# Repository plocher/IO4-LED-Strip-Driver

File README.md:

# I2C-LEDStripDriver
## License: CERN Open Hardware Licence v1.2

PWM Driver board for high current LED strips

An IO4 appliance that takes 4x PWM signals and drives 4x LED strips (RGB + White) at up to 2A each at 12v

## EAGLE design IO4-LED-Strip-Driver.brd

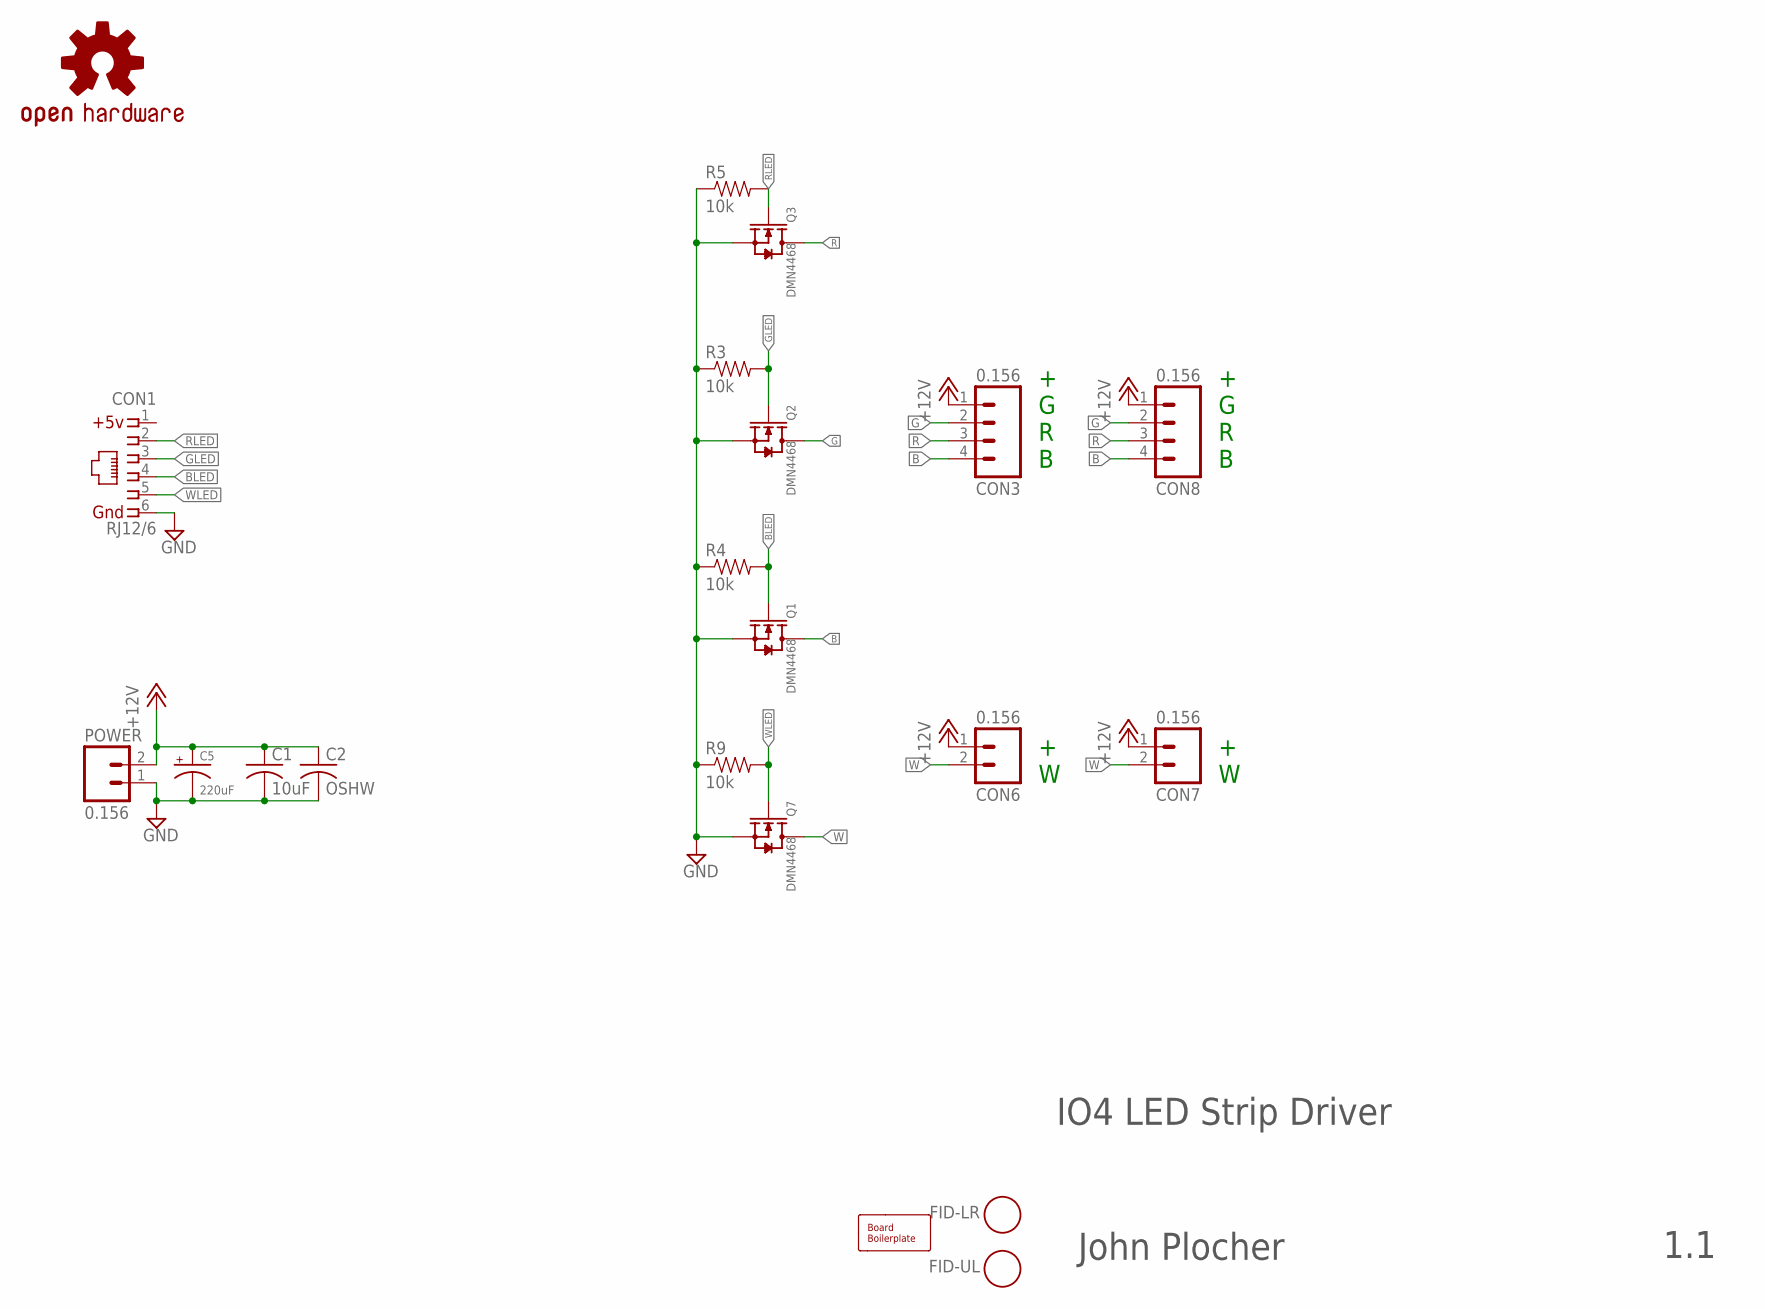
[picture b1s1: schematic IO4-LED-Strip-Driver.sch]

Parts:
BOARD1: BOARD; BOARD-DINRAIL-3.17INX10CM
C1: 10uF; 0603-CAP
C2: OSHW; 0603-CAP
C5: 220uF; 0810-CAP
CON1: RJ12/6; RJ25-INVERTED
CON3, CON8: 0.156; MSTBA4
CON6, CON7: 0.156; MSTBA2
FID-LR: FIDUCIAL; FIDUCIAL_1MM
FID-UL: FIDUCIAL; FIDUCIAL_1MM
OSHW1: OSHW; OSHW-LOGO-L
POWER: 0.156; MSTBA2
Q1, Q2, Q3, Q7: DMN4468; SO08
R3, R4, R5, R9: 10k; 0603-RES

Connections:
1: CON1.1
+12V: C1.1, C2.1, C5.+, CON3.1, CON6.1 (A), CON7.1 (A), CON8.1, POWER.2 (B)
B: CON3.4, CON8.4, Q1.5 (D), Q1.6 (D), Q1.7 (D), Q1.8 (D)
BLED: CON1.4, Q1.4 (G), R4.2
G: CON3.2, CON8.2, Q2.5 (D), Q2.6 (D), Q2.7 (D), Q2.8 (D)
GLED: CON1.3, Q2.4 (G), R3.2
GND: C1.2, C2.2, C5.-, CON1.6, POWER.1 (A), Q1.1 (S), Q1.2 (S), Q1.3 (S), Q2.1 (S), Q2.2 (S), Q2.3 (S), Q3.1 (S), Q3.2 (S), Q3.3 (S), Q7.1 (S), Q7.2 (S), Q7.3 (S), R3.1, R4.1, R5.1, R9.1
R: CON3.3, CON8.3, Q3.5 (D), Q3.6 (D), Q3.7 (D), Q3.8 (D)
RLED: CON1.2, Q3.4 (G), R5.2
W: CON6.2 (B), CON7.2 (B), Q7.5 (D), Q7.6 (D), Q7.7 (D), Q7.8 (D)
WLED: CON1.5, Q7.4 (G), R9.2

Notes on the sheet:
IO4 LED Strip Driver
John Plocher
1.1
+ G R B
+ W

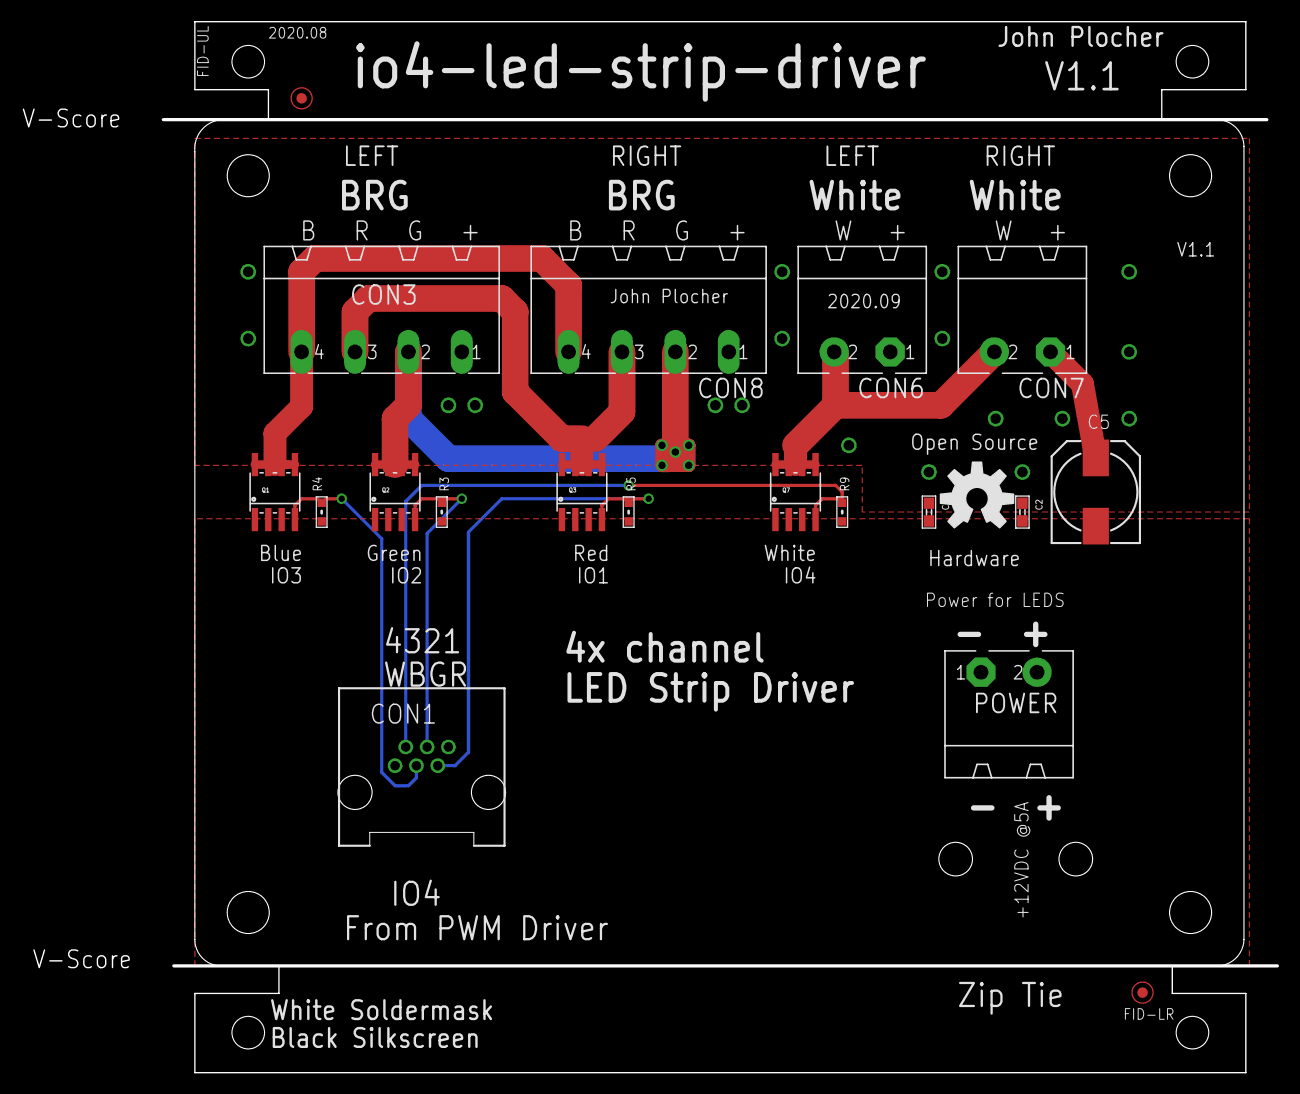
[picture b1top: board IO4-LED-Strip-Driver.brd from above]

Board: 2 copper layers, 119.4 x 99.8 mm, 21 parts (0 on the bottom side), 10 nets.

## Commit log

2020-07-28 Initial version
2020-07-28 renamed
2020-07-28 version#
2020-08-05 silkscreen changes
2020-08-05 Labeled channels on silkscreen, fixed bottom silk layers
2020-08-12 FID placement & rerouting
2020-09-16 Swapped R and G connector locations to match LED string wiring
2020-10-05 added values for connectors
2020-10-06 normalized values
